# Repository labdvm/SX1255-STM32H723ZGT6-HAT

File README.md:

# SX1255-STM32H723ZGT6-HAT
This is SX1255 HAT for STM32H723ZGT6 board
This is preliminary the next generation hotspot
V 1.0
Z32IT

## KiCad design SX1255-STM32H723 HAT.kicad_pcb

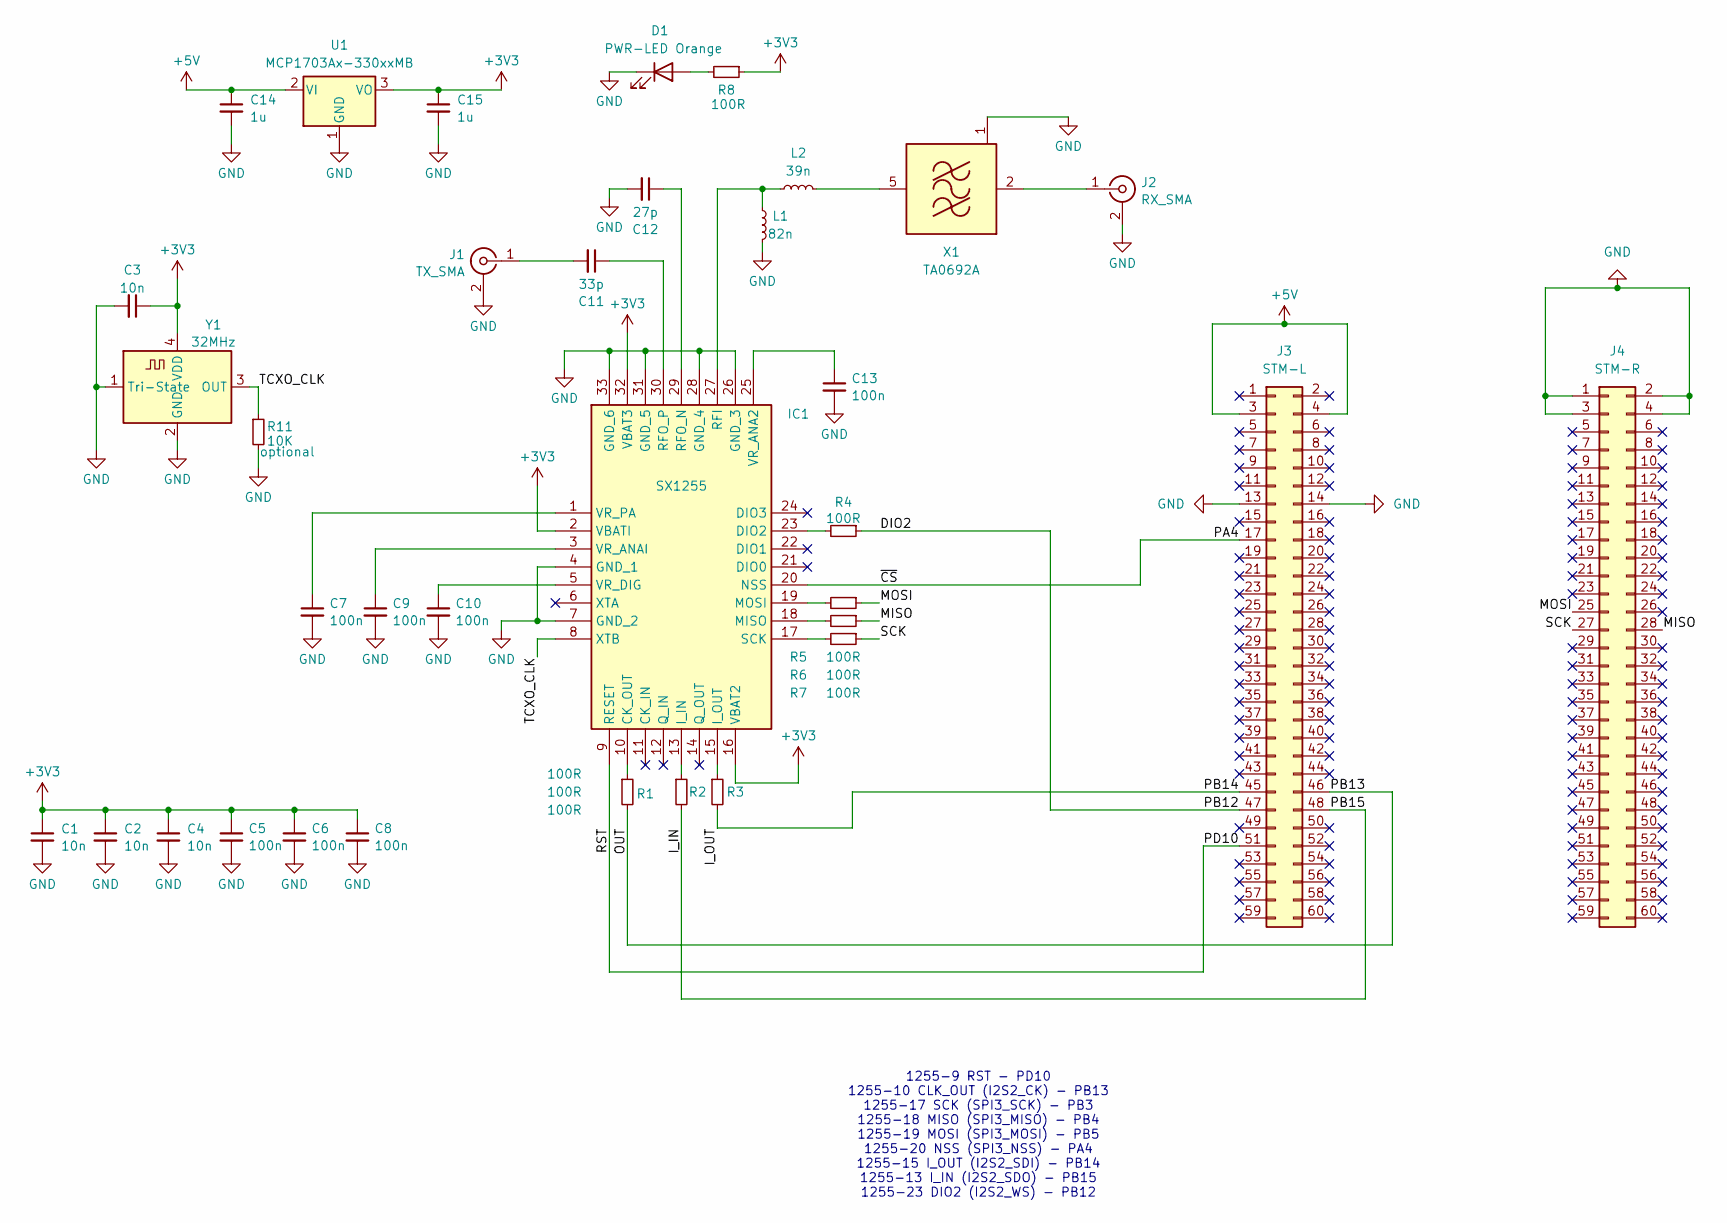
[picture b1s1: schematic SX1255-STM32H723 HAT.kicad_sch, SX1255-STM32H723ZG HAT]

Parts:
C1, C2, C3, C4: 10n; C_0805_2012Metric; MPN C0603C103M4REC7411
C5, C6, C7, C8, C9, C10, C13: 100n; C_0805_2012Metric; MPN 06035G104ZAT2A
C11: 33p; C_0805_2012Metric; MPN VJ0603A330KXAPW1BC
C12: 27p; C_0805_2012Metric; MPN AC0603JRNPO9BN270
C14, C15: 1u; C_0805_2012Metric; MPN C0603C103M4REC7411
D1: PWR-LED Orange; LED_0805_2012Metric
IC1: SX1255; QFN-32-1EP_5x5mm_P0.5mm_EP3.1x3.1mm_ThermalVias; MPN SX1255IWLTRT
J1: TX_SMA; SMA_Amphenol_901-144_Vertical; MPN RF2-04A-T-00-50-G
J2: RX_SMA; SMA_Amphenol_901-144_Vertical; MPN RF2-04A-T-00-50-G
J3: STM-L; PinSocket_2x30_P2.54mm_Vertical
J4: STM-R; PinSocket_2x30_P2.54mm_Vertical
L1: 82n; L_0805_2012Metric; MPN AISC-0603-R082J-T
L2: 39n; L_0805_2012Metric; MPN AISC-0603-R039J-T
R1, R2, R3, R4, R5, R6, R7, R8: 100R; R_0805_2012Metric; MPN CRCW0603100RFKECC
R11: 10K; R_0805_2012Metric; MPN CRCW0603100RFKECC
U1: MCP1703Ax-330xxMB; SOT-89-3
X1: TA0692A; Filter_SAW-6_3.8x3.8mm
Y1: 32MHz; Crystal_SMD_3225-4Pin_3.2x2.5mm; MPN ECS-TXO-20CSMV4-320-AY-TR

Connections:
+3V3: C1.1, C2.1, C3.1, C4.1, C5.1, C6.1, C8.1, C15.1, IC1.2 (VBATI), IC1.16 (VBAT2), IC1.32 (VBAT3), R8.1, U1.3 (VO), Y1.4 (VDD)
+5V: C14.1, J3.3, J3.4, U1.2 (VI)
/DIO2: J3.47, R4.1
/I_IN: J3.48, R2.2
/I_OUT: J3.45, R3.2
/MISO: J4.28, R6.1
/MOSI: J4.25, R5.1
/OUT: J3.46, R1.2
/PA4: IC1.20 (NSS), J3.17
/PD10: IC1.9 (RESET), J3.51
/SCK: J4.27, R7.1
/TCXO_CLK: IC1.8 (XTB), R11.1, Y1.3 (OUT)
GND: C1.2, C2.2, C3.2, C4.2, C5.2, C6.2, C7.2, C8.2, C9.2, C10.2, C12.2, C13.2, C14.2, C15.2, D1.1 (K), IC1.4 (GND_1), IC1.7 (GND_2), IC1.26 (GND_3), IC1.28 (GND_4), IC1.31 (GND_5), IC1.33 (GND_6), J1.2 (Ext), J2.2 (Ext), J3.13, J3.14, J4.1, J4.2, J4.3, J4.4, L1.1, R11.2, U1.1 (GND), X1.1 (GND), X1.3 (GND), X1.4 (GND), X1.6 (GND), Y1.1 (Tri-State), Y1.2 (GND)
unnamed: D1.2 (A), R8.2
unnamed: IC1.10 (CK_OUT), R1.1
unnamed: IC1.23 (DIO2), R4.2
unnamed: IC1.13 (I_IN), R2.1
unnamed: IC1.15 (I_OUT), R3.1
unnamed: IC1.18 (MISO), R6.2
unnamed: IC1.19 (MOSI), R5.2
unnamed: IC1.27 (RFI), L1.2, L2.2
unnamed: C12.1, IC1.29 (RFO_N)
unnamed: C11.1, IC1.30 (RFO_P)
unnamed: IC1.17 (SCK), R7.2
unnamed: C13.1, IC1.25 (VR_ANA2)
unnamed: C9.1, IC1.3 (VR_ANAI)
unnamed: C10.1, IC1.5 (VR_DIG)
unnamed: C7.1, IC1.1 (VR_PA)
unnamed: C11.2, J1.1 (In)
unnamed: J2.1 (In), X1.2 (IN)
unnamed: L2.1, X1.5 (OUT)

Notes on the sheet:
1255-9 RST - PD10 1255-10 CLK_OUT (I2S2_CK) - PB13 1255-17 SCK (SPI3_SCK) - PB3 1255-18 MISO (SPI3_MISO) - PB4 1255-19 MOSI (SPI3_MOSI) - PB5 1255-20 NSS (SPI3_NSS) - PA4 1255-15 I_OUT (I2S2_SDI) - PB14 1255-13 I_IN (I2S2_SDO) - PB15 1255-23 DIO2 (I2S2_WS) - PB12

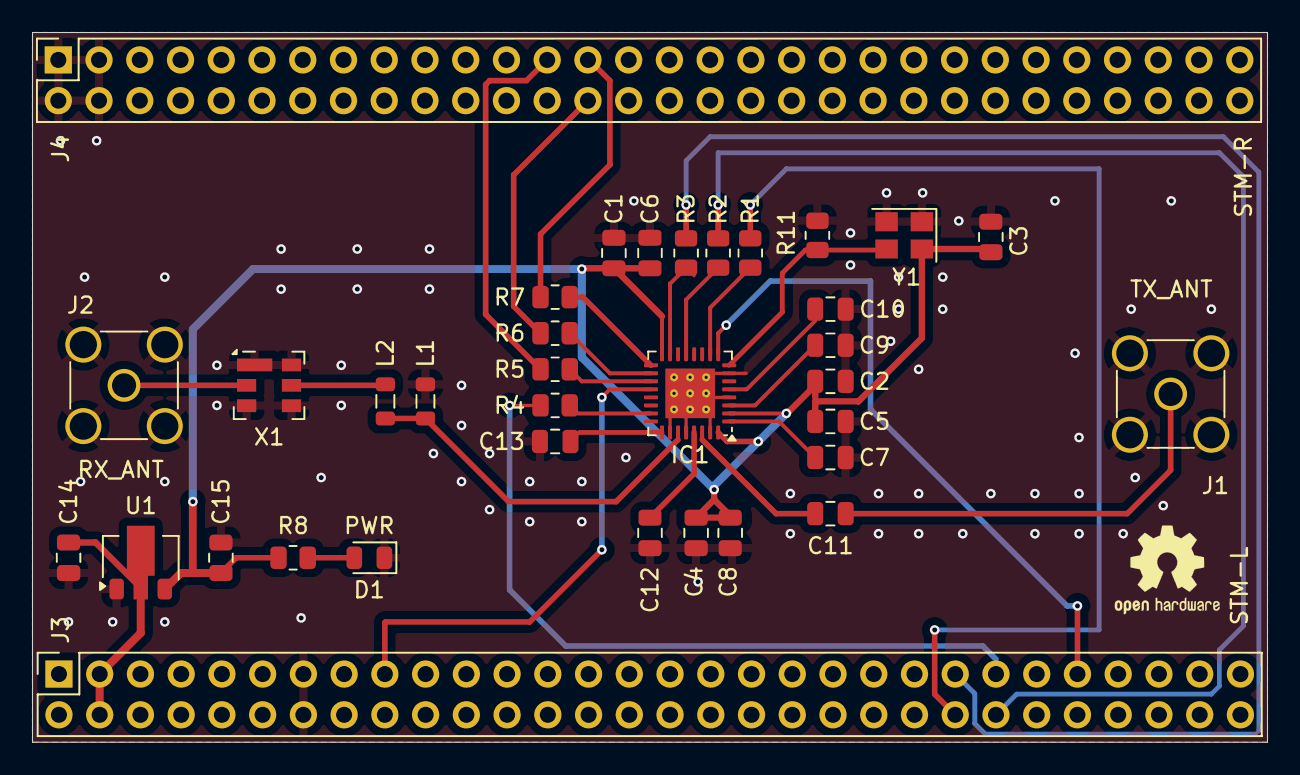
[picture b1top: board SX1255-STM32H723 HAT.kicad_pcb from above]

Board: 2 copper layers, 77.0 x 44.2 mm, 35 parts (0 on the bottom side), 31 nets.

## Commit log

2026-01-07 Fix version number format in README.md
